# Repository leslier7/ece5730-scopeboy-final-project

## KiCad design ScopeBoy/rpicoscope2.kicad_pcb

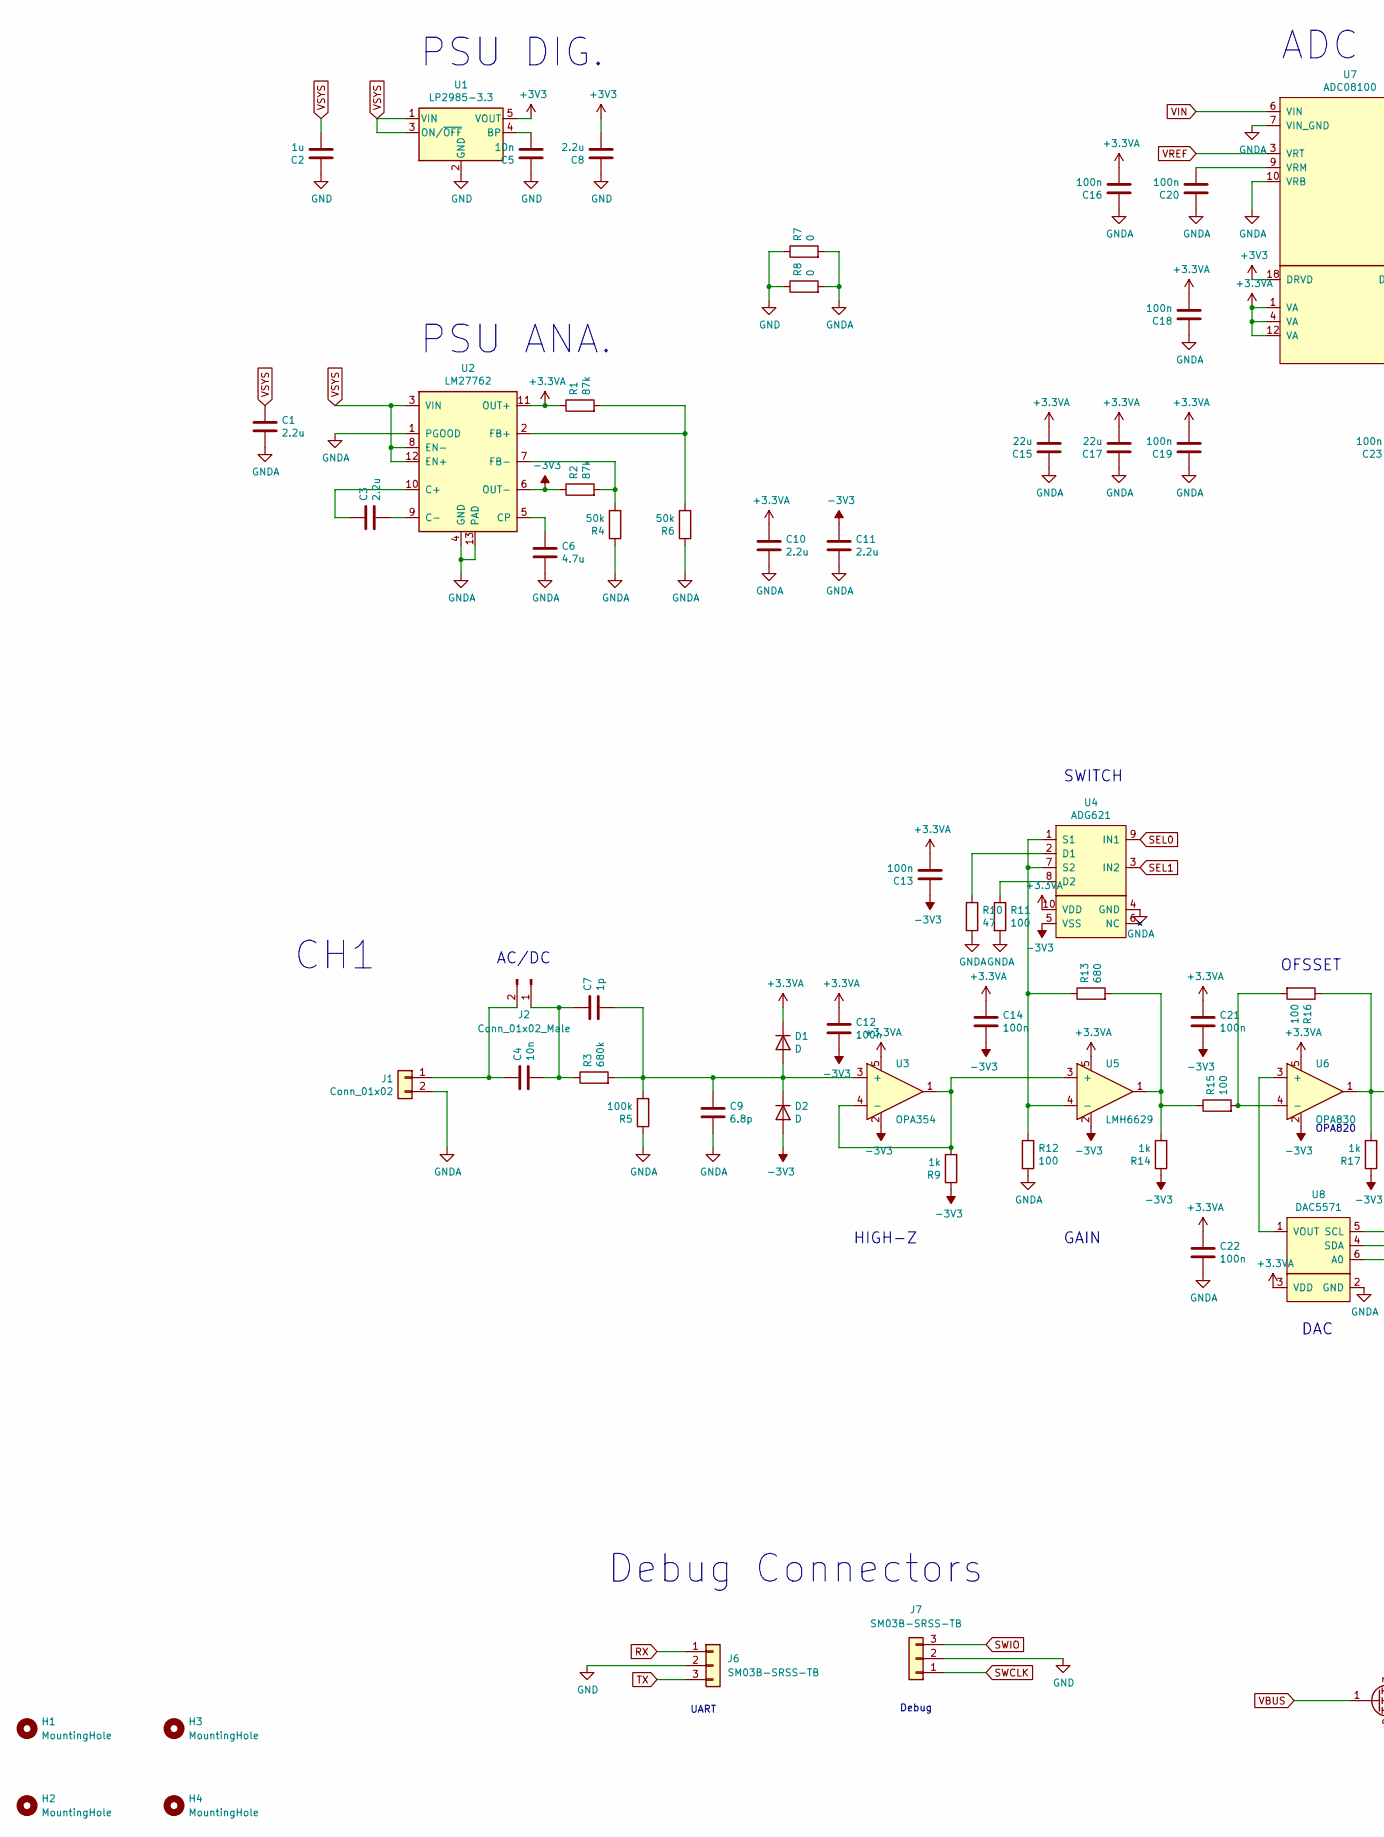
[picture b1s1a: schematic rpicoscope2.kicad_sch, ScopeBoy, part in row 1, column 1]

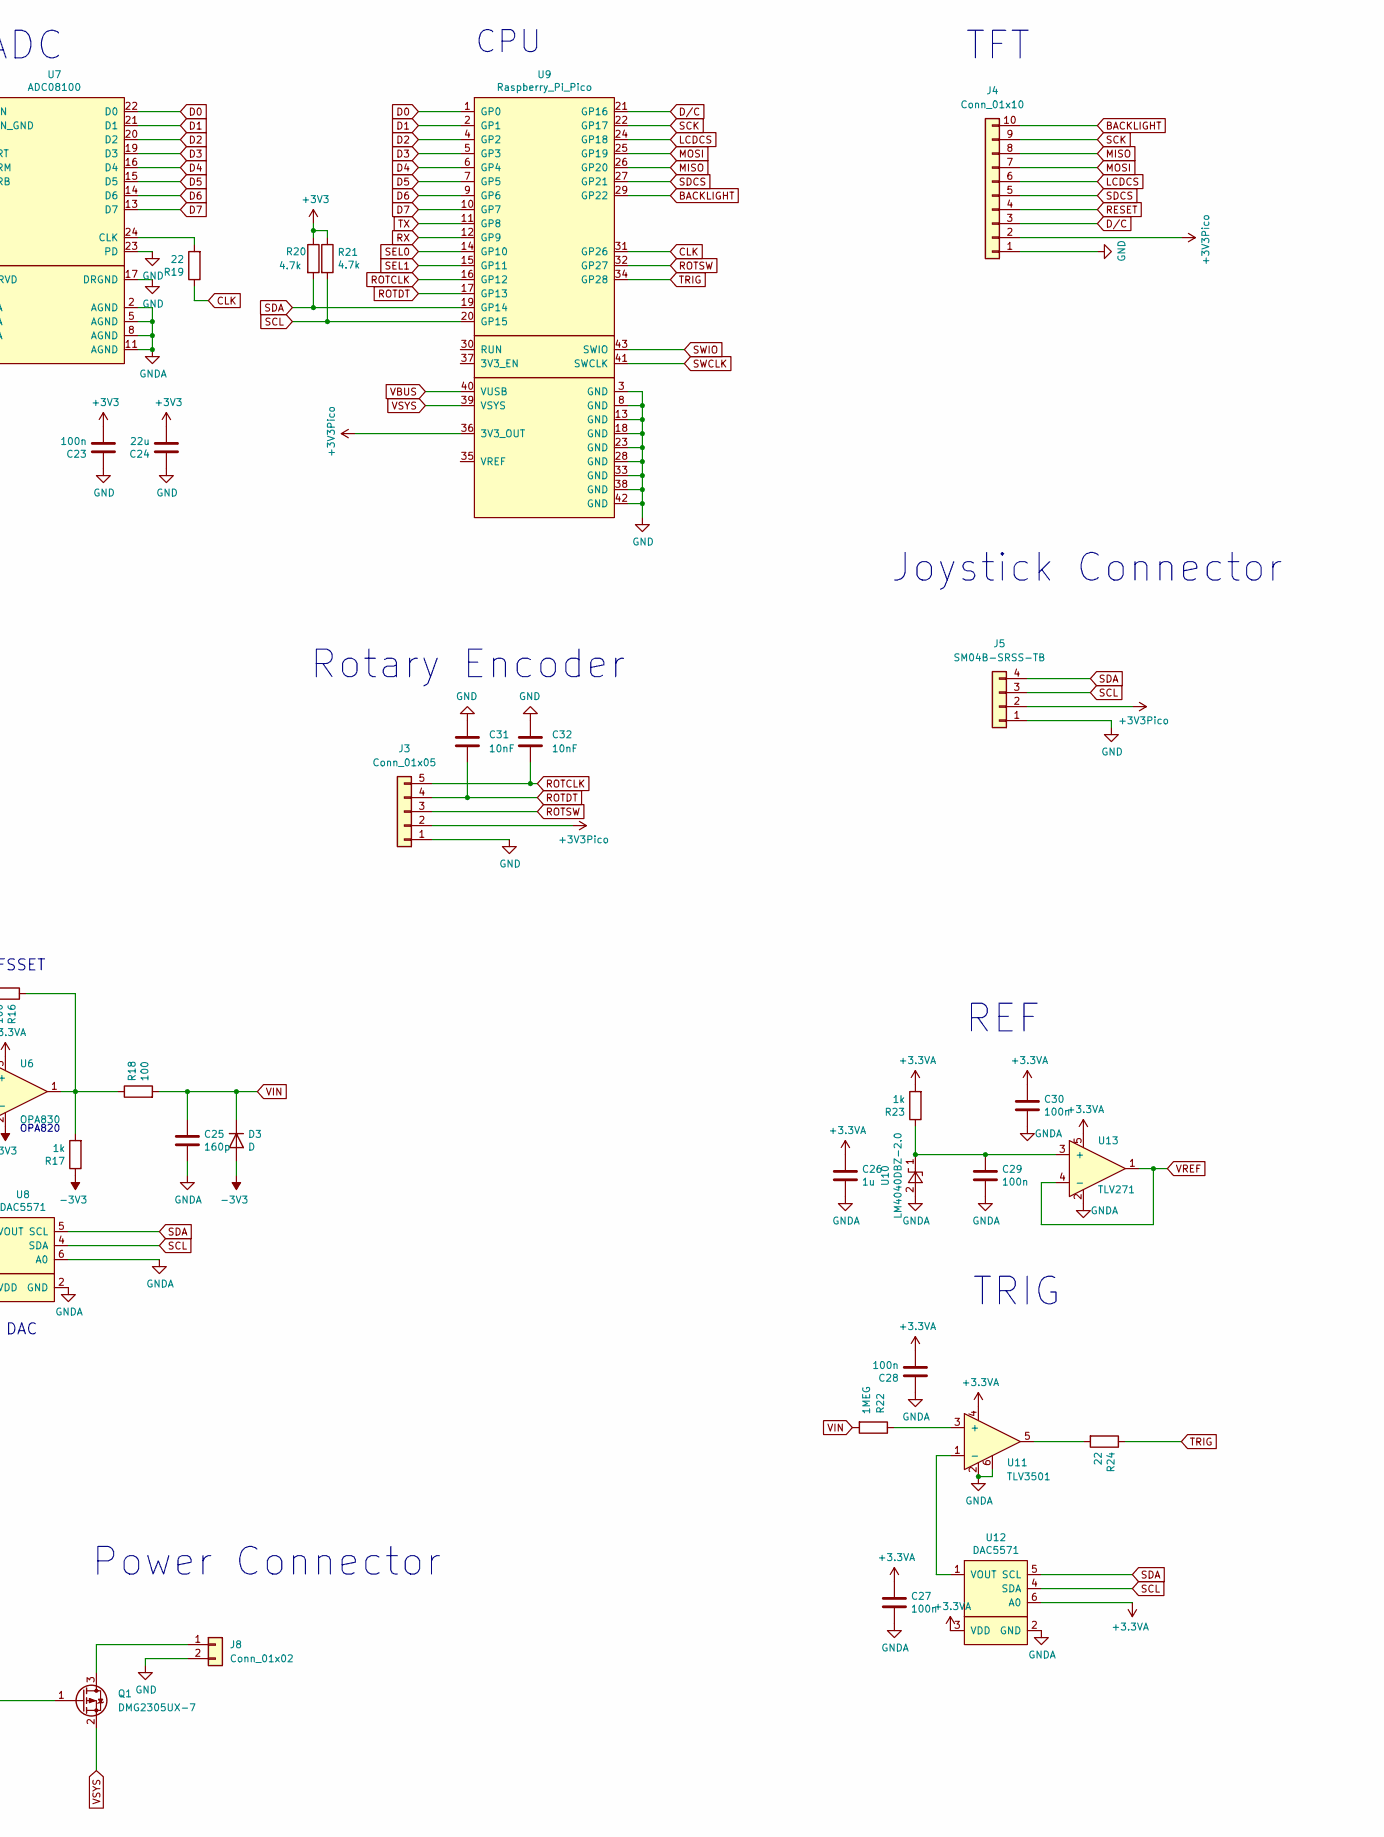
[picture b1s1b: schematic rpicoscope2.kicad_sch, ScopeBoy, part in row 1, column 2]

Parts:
C1, C3, C8, C10, C11: 2.2u; C_0603_1608Metric; MFR. Part # CL10A225KO8NNNC; LCSC Part # C23630
C2, C26: 1u; C_0603_1608Metric; MFR. Part # CL10A105KB8NNNC; LCSC Part # C15849
C4, C5: 10n; C_0603_1608Metric; MFR. Part # 0603B103K500NT; LCSC Part # C57112
C6: 4.7u; C_0603_1608Metric; MFR. Part # CL10A475KO8NNNC; LCSC Part # C19666
C7: 1p; C_0603_1608Metric; MFR. Part # CC0603CRNPO9BN1R0; LCSC Part # C277513
C9: 6.8p; C_0603_1608Metric; MFR. Part # CL10C6R8CB8NNNC; LCSC Part # C318672
C12, C13, C14, C16, C18, C19, C20, C21, C22, C23, C27, C28, C29, C30: 100n; C_0603_1608Metric; MFR. Part # CC0603KRX7R9BB104; LCSC Part # C14663
C15, C17, C24: 22u; C_0603_1608Metric; MFR. Part # CL10A226MQ8NRNC; LCSC Part # C59461
C25: 160p; C_0603_1608Metric; MFR. Part # FN18X104K160PSG; LCSC Part # C235729
C31, C32: 10nF; C_0603_1608Metric; MFR. Part # CL10B103KB8NNNC; LCSC Part # C1589
D1, D2, D3: D; D_0603_1608Metric
H1, H2, H3, H4: MountingHole; MountingHole_3.2mm_M3_Pad_TopBottom
J1: Conn_01x02; SMA_Samtec_SMA-J-P-X-ST-EM1_EdgeMount
J2: Conn_01x02_Male; PinHeader_1x02_P1.00mm_Vertical_SMD_Pin1Left
J3: Conn_01x05; PinHeader_1x05_P2.54mm_Vertical
J4: Conn_01x10; PinHeader_1x10_P2.54mm_Vertical
J5: SM04B-SRSS-TB; JST_SH_SM04B-SRSS-TB_1x04-1MP_P1.00mm_Horizontal; MFR. Part # SM04B-SRSS-TB(LF)(SN); LCSC Part # C160404
J6, J7: SM03B-SRSS-TB; JST_SH_SM03B-SRSS-TB_1x03-1MP_P1.00mm_Horizontal; MFR. Part # SM03B-SRSS-TB(LF)(SN); LCSC Part # C160403
J8: Conn_01x02; PinHeader_1x02_P2.54mm_Vertical
Q1: DMG2305UX-7; SOT-23-3; MFR. Part # DMG2305UX-7; LCSC Part # C150470
R1, R2: 87k; R_0603_1608Metric; MFR. Part # 0603WAF8202T5E; LCSC Part # C23254
R3: 680k; R_0603_1608Metric; MFR. Part # 0603WAF6803T5E; LCSC Part # C25822
R4, R6: 50k; R_0603_1608Metric; MFR. Part # 0603WAF1503T5E; LCSC Part # C22807
R5: 100k; R_0603_1608Metric; MFR. Part # 0603WAF1003T5E; LCSC Part # C25803
R7, R8: 0; R_0603_1608Metric; MFR. Part # 0603WAF0000T5E; LCSC Part # C21189
R9, R14, R17, R23: 1k; R_0603_1608Metric; MFR. Part # 0603WAF1001T5E; LCSC Part # C21190
R10: 47; R_0603_1608Metric; MFR. Part # 0603WAF470JT5E; LCSC Part # C23182
R11, R12, R15, R16, R18: 100; R_0603_1608Metric; MFR. Part # 0603WAF1000T5E; LCSC Part # C22775
R13: 680; R_0603_1608Metric; MFR. Part # 0603WAF6801T5E; LCSC Part # C23212
R19, R24: 22; R_0603_1608Metric; MFR. Part # 0603WAF220JT5E; LCSC Part # C23345
R20, R21: 4.7k; R_0603_1608Metric; MFR. Part # 0603WAF4701T5E; LCSC Part # C23162
R22: 1MEG; R_0603_1608Metric; MFR. Part # ERJ3EKF1004V; LCSC Part # C193390
U1: LP2985-3.3; SOT-23-5; MFR. Part # LP2985-33DBVR; LCSC Part # C95414
U2: LM27762; WSON-12-1EP_3x2mm_P0.5mm_EP1x2.65_ThermalVias; MFR. Part # LM27762DSSR; LCSC Part # C473398
U3: OPA354; SOT-23-5; MFR. Part # OPA354AIDBVR; LCSC Part # C36384
U4: ADG621; MSOP-10_3x3mm_P0.5mm; LCSC Part # C208597
U5: LMH6629; SOT-23-5; LCSC Part # C206003
U6: OPA830; SOT-23-5; MRF. Part # OPA830IDBVR; LCSC Part # C2058414
U7: ADC08100; TSSOP-24_4.4x7.8mm_P0.65mm; LCSC Part # C701581
U8, U12: DAC5571; SOT-23-6; LCSC Part # C24061
U9: Raspberry_Pi_Pico; RPi_Pico_SMD_TH; MFR. Part # SC0915; LCSC Part # C7203002
U10: LM4040DBZ-2.0; SOT-23; MFR. Part # LM4040A20IDBZR; LCSC Part # C127070
U11: TLV3501; SOT-23-6; LCSC Part # C193413
U13: TLV271; SOT-23-5; LCSC Part # C181500

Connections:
+3.3VA: C10.1, C12.1, C13.2, C14.1, C15.2, C16.2, C17.2, C18.2, C19.2, C21.1, C22.1, C26.1, C27.1, C28.2, C30.1, D1.1 (K), R1.1, R23.2, U2.11 (OUT+), U3.5, U4.10 (VDD), U5.5, U6.5, U7.1 (VA), U7.4 (VA), U7.12 (VA), U8.3 (VDD), U11.4, U12.3 (VDD), U12.6 (A0), U13.5
+3V3: C8.2, C23.2, C24.2, R20.1, R21.1, U1.5 (VOUT), U7.18 (DRVD)
+3V3Pico: J3.2, J4.2, J5.2, U9.36 (3V3_OUT)
-3V3: C11.1, C12.2, C13.1, C14.2, C21.2, D2.2 (A), D3.2 (A), R2.1, R9.1, R14.1, R17.1, U2.6 (OUT-), U3.2, U4.5 (VSS), U5.2, U6.2
BACKLIGHT: J4.10, U9.29 (GP22)
CLK: R19.1, U9.31 (GP26)
D0: U7.22 (D0), U9.1 (GP0)
D1: U7.21 (D1), U9.2 (GP1)
D2: U7.20 (D2), U9.4 (GP2)
D3: U7.19 (D3), U9.5 (GP3)
D4: U7.16 (D4), U9.6 (GP4)
D5: U7.15 (D5), U9.7 (GP5)
D6: U7.14 (D6), U9.9 (GP6)
D7: U7.13 (D7), U9.10 (GP7)
D/C: J4.3, U9.21 (GP16)
GND: C2.1, C5.1, C8.1, C23.1, C24.1, C31.1, C32.1, J3.1, J4.1, J5.1, J6.2, J7.2, J8.2, R7.1, R8.1, U1.2 (GND), U7.17 (DRGND), U7.23 (PD), U9.3 (GND), U9.8 (GND), U9.13 (GND), U9.18 (GND), U9.23 (GND), U9.28 (GND), U9.33 (GND), U9.38 (GND), U9.42 (GND)
GNDA: C1.2, C6.2, C9.2, C10.2, C11.2, C15.1, C16.1, C17.1, C18.1, C19.1, C20.1, C22.2, C25.2, C26.2, C27.2, C28.1, C29.2, C30.2, J1.2, R4.1, R5.1, R6.1, R7.2, R8.2, R10.2, R11.2, R12.2, U2.1 (PGOOD), U2.4 (GND), U2.13 (PAD), U4.4 (GND), U7.2 (AGND), U7.5 (AGND), U7.7 (VIN_GND), U7.8 (AGND), U7.10 (VRB), U7.11 (AGND), U8.2 (GND), U8.6 (A0), U10.2 (A), U11.2, U11.6, U12.2 (GND), U13.2
LCDCS: J4.6, U9.24 (GP18)
MISO: J4.8, U9.26 (GP20)
MOSI: J4.7, U9.25 (GP19)
unnamed: C7.2, C9.1, D1.2 (A), D2.1 (K), R3.2, R5.2, U3.3 (+)
unnamed: C4.1, J1.1, J2.2
unnamed: C4.2, C7.1, J2.1, R3.1
unnamed: J8.1, Q1.3 (D)
unnamed: R13.2, R14.2, R15.1, U5.1
unnamed: R16.1, R17.2, R18.1, U6.1
unnamed: R24.2, U11.5
unnamed: C5.2, U1.4 (BP)
unnamed: C3.1, U2.10 (C+)
unnamed: C3.2, U2.9 (C-)
unnamed: C6.1, U2.5 (CP)
unnamed: R1.2, R6.2, U2.2 (FB+)
unnamed: R2.2, R4.2, U2.7 (FB-)
unnamed: R9.2, U3.1, U3.4 (-), U5.3 (+)
unnamed: R10.1, U4.2 (D1)
unnamed: R11.1, U4.8 (D2)
unnamed: R12.1, R13.1, U4.1 (S1), U4.7 (S2), U5.4 (-)
unnamed: U6.3 (+), U8.1 (VOUT)
unnamed: R15.2, R16.2, U6.4 (-)
unnamed: R19.2, U7.24 (CLK)
unnamed: C20.2, U7.9 (VRM)
unnamed: C29.1, R23.1, U10.1 (K), U13.3 (+)
unnamed: R22.1, U11.3 (+)
unnamed: U11.1 (-), U12.1 (VOUT)
RESET: J4.4
ROTCLK: C32.2, J3.5, U9.16 (GP12)
ROTDT: C31.2, J3.4, U9.17 (GP13)
ROTSW: J3.3, U9.32 (GP27)
RX: J6.1, U9.12 (GP9)
SCK: J4.9, U9.22 (GP17)
SCL: J5.3, R21.2, U8.4 (SDA), U9.20 (GP15), U12.4 (SDA)
SDA: J5.4, R20.2, U8.5 (SCL), U9.19 (GP14), U12.5 (SCL)
SDCS: J4.5, U9.27 (GP21)
SEL0: U4.9 (IN1), U9.14 (GP10)
SEL1: U4.3 (IN2), U9.15 (GP11)
SWCLK: J7.1, U9.41 (SWCLK)
SWIO: J7.3, U9.43 (SWIO)
TRIG: R24.1, U9.34 (GP28)
TX: J6.3, U9.11 (GP8)
VBUS: Q1.1 (G), U9.40 (VUSB)
VIN: C25.1, D3.1 (K), R18.2, R22.2, U7.6 (VIN)
VREF: U7.3 (VRT), U13.1, U13.4 (-)
VSYS: C1.1, C2.2, Q1.2 (S), U1.1 (VIN), U1.3 (ON/~OFF), U2.3 (VIN), U2.8 (EN-), U2.12 (EN+), U9.39 (VSYS)

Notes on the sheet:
DAC
PSU DIG.
CPU
REF
Debug
Power Connector
CH1
TFT
TRIG
GAIN
Rotary Encoder
ADC
OFSSET
Debug Connectors
SWITCH
HIGH-Z
Joystick Connector
AC/DC
UART
PSU ANA.
OPA820

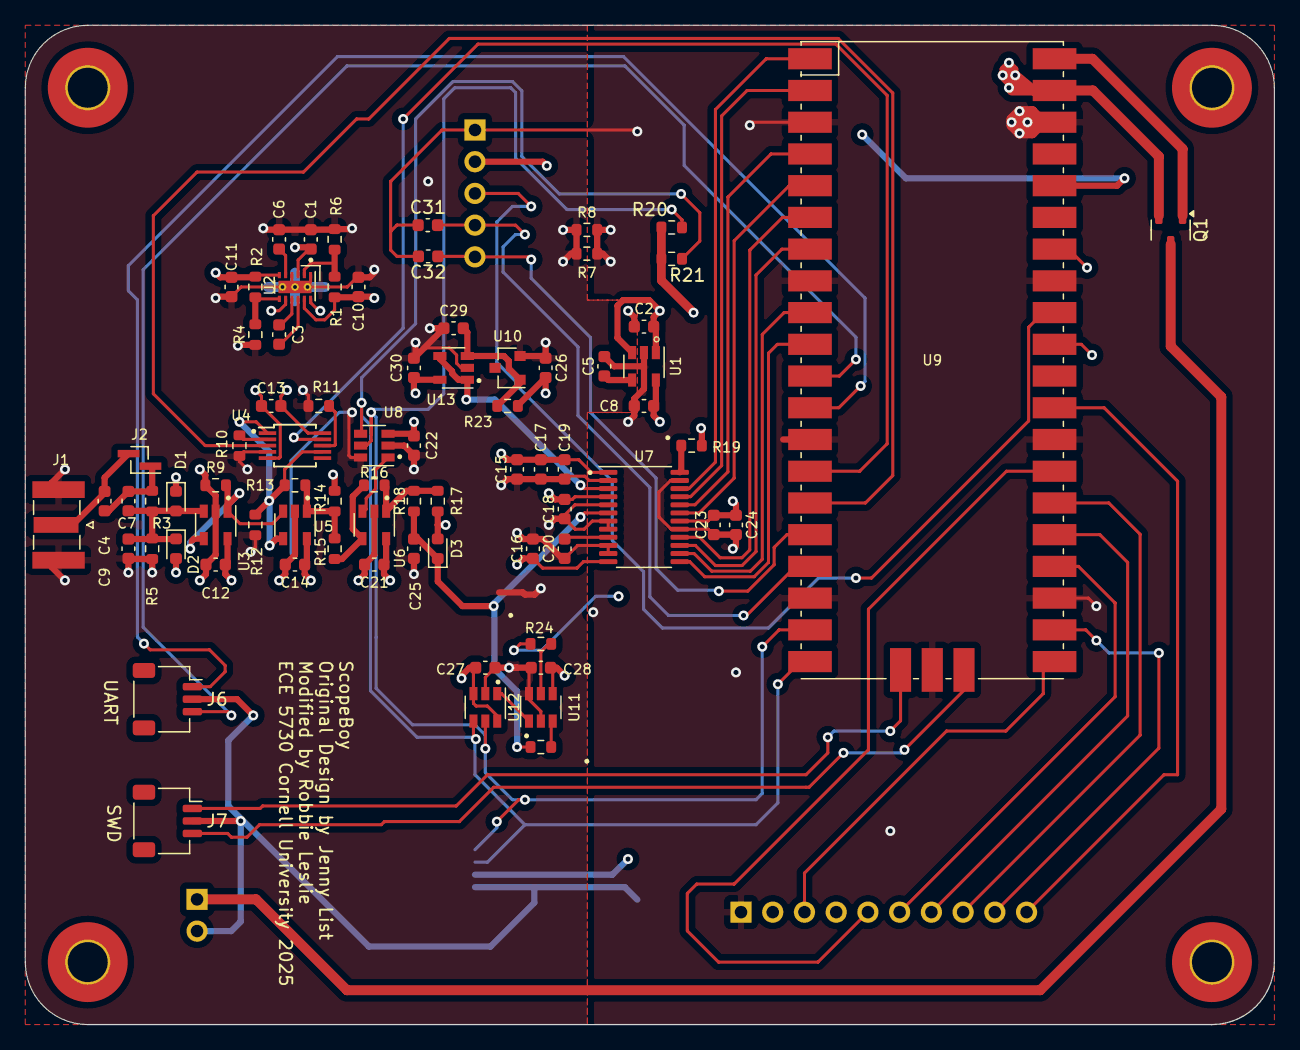
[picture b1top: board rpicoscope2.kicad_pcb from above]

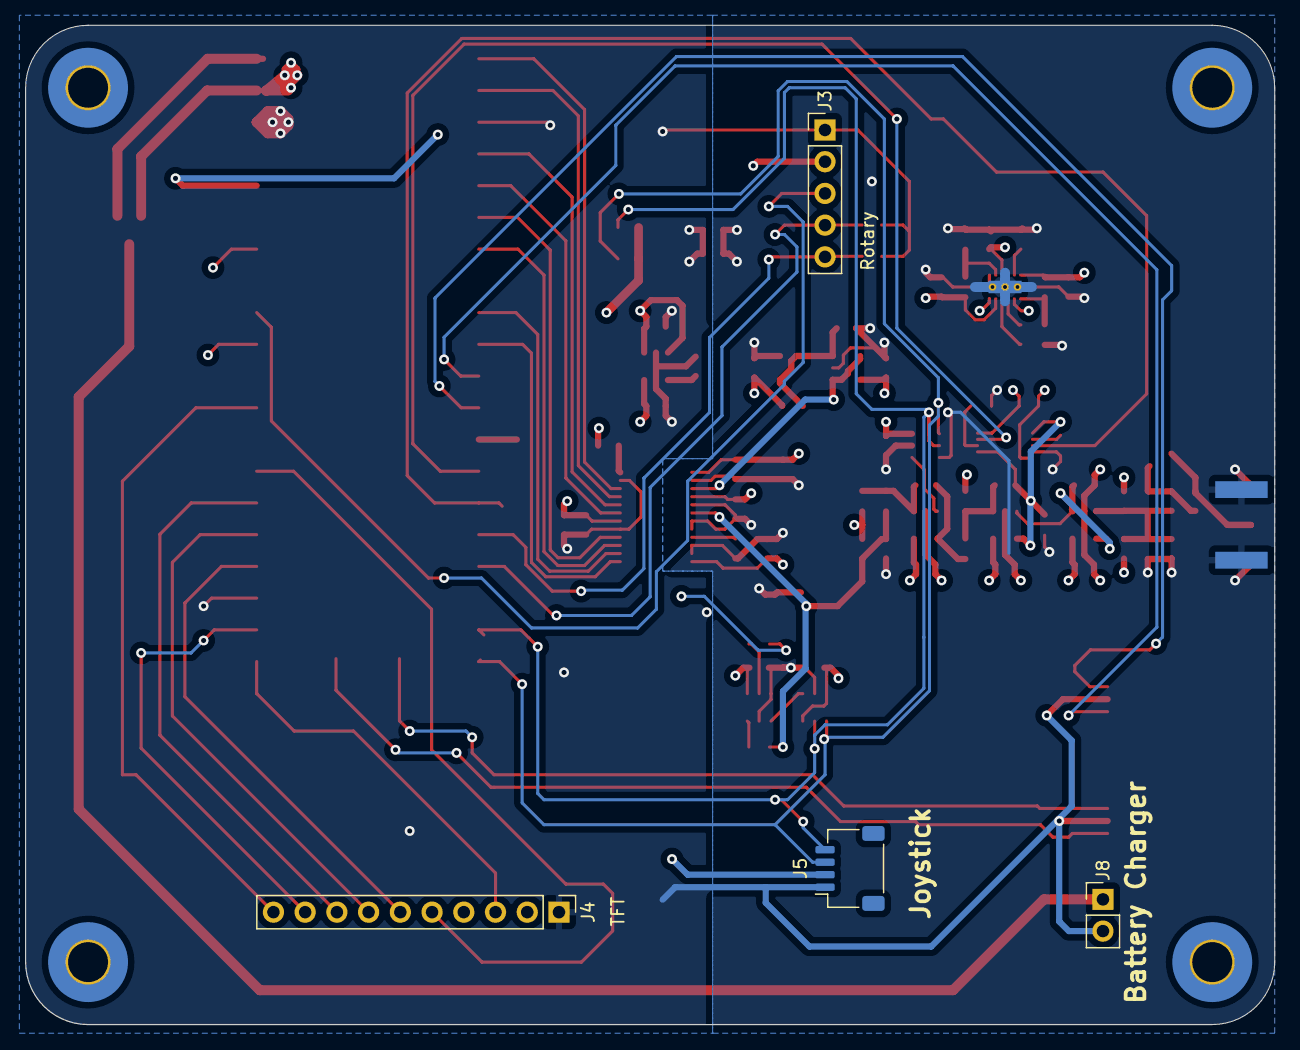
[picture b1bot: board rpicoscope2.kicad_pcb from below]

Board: 4 copper layers, 100.0 x 80.0 mm, 85 parts (4 on the bottom side), 62 nets.

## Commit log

2025-11-13 Final project skeleton
2025-11-13 Started work on rotary driver
2025-11-14 Started work on PCB
2025-11-14 Initial version of the PCB done
2025-11-14 Added caps on encoder
2025-11-17 Final revision of PCB. Updated some components
2025-11-17 Quick cap replacement (same footprint)
2025-11-17 refil
2025-11-20 Got rotary mostly working
2025-11-20 Added 3D models for missing components
2025-12-04 Fix the commit history for work done on final project
2025-12-04 Started working on dac
2025-12-04 Got DAC working
2025-12-07 Got ADC working
2025-12-08 Got reading the waveform working, and started work on trigger
2025-12-08 Edited schematic, changed default trigger, and working on gain mode
2025-12-08 Updated schematic
2025-12-16 Adds the website template for the final project
2025-12-16 Fixed website include and added schematics
2025-12-16 Added gitignore
2025-12-16 Continued work on website
2025-12-17 Update website intro and design documentation
2025-12-17 Expand High Level Design logical structure
2025-12-19 Added images from demo
2025-12-19 Add 3D render images and update website content
    - Add 3D overall view to Project Introduction
    - Add 3 exploded assembly views to Hardware details
    - Expand Hardware/Software Tradeoffs section
    - Remove descriptive headers from intro sections
2025-12-20 Update Appendix D and AI use section
    - Add detailed task breakdown for Immanuel Varghese Koshy
    - Expand AI use discussion with tools, applications, verification, and unused content
2025-12-20 Updated to final version of code, and continued work on website
2025-12-20 Final version of website
2025-12-20 Added iDocs copyright paragraph
